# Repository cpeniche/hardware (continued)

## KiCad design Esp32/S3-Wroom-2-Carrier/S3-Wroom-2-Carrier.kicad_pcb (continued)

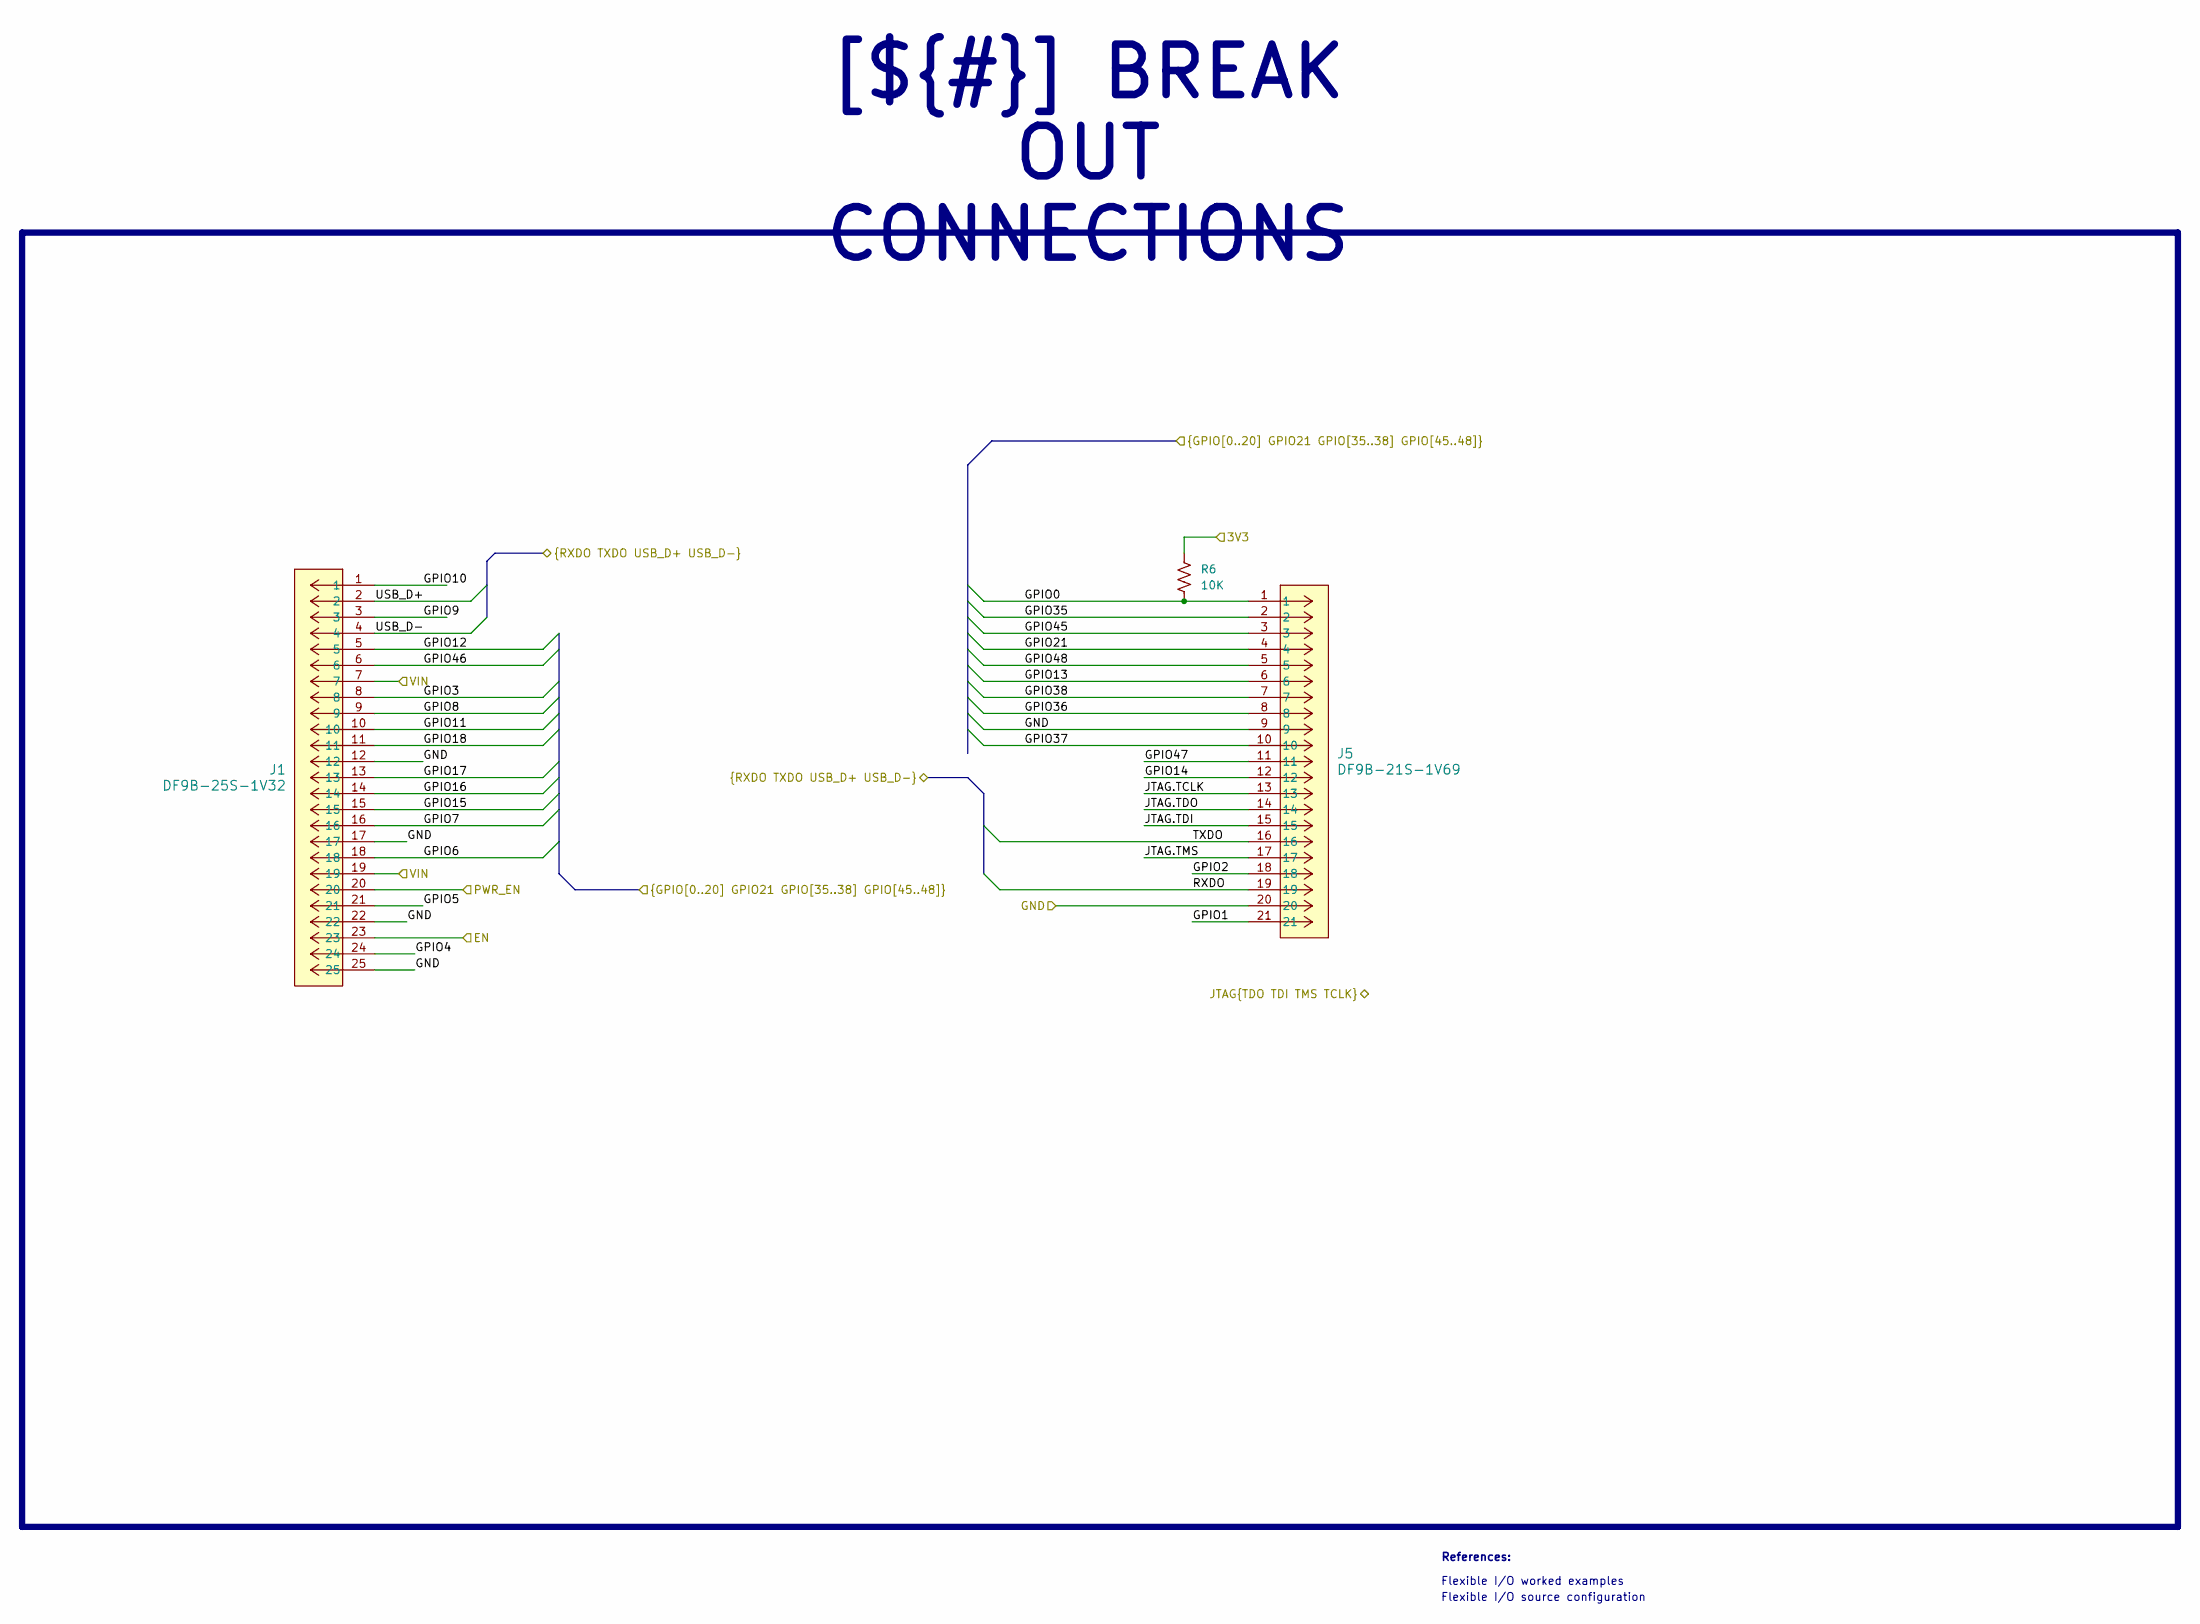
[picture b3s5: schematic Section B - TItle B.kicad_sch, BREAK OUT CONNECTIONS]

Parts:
J1: DF9B-25S-1V32; CON9_1X25_DL_DF9_HIR
J5: DF9B-21S-1V69; CONN_DF9B-21S-1V_21P_HIR
R6: 10K; R_0805_2012Metric_Pad1.20x1.40mm_HandSolder

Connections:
+3V3: R6.1; also elsewhere on the board
/Project Architecture/Break Out Connection/GPIO0: J5.1, R6.2; also elsewhere on the board
/Project Architecture/Break Out Connection/GPIO1: J5.21; also elsewhere on the board
/Project Architecture/Break Out Connection/GPIO2: J5.18; also elsewhere on the board
/Project Architecture/Break Out Connection/GPIO3: J1.8; also elsewhere on the board
/Project Architecture/Break Out Connection/GPIO4: J1.24; also elsewhere on the board
/Project Architecture/Break Out Connection/GPIO5: J1.21; also elsewhere on the board
/Project Architecture/Break Out Connection/GPIO6: J1.18; also elsewhere on the board
/Project Architecture/Break Out Connection/GPIO7: J1.16; also elsewhere on the board
/Project Architecture/Break Out Connection/GPIO8: J1.9; also elsewhere on the board
/Project Architecture/Break Out Connection/GPIO9: J1.3; also elsewhere on the board
/Project Architecture/Break Out Connection/GPIO10: J1.1; also elsewhere on the board
/Project Architecture/Break Out Connection/GPIO11: J1.10; also elsewhere on the board
/Project Architecture/Break Out Connection/GPIO12: J1.5; also elsewhere on the board
/Project Architecture/Break Out Connection/GPIO13: J5.6; also elsewhere on the board
/Project Architecture/Break Out Connection/GPIO14: J5.12; also elsewhere on the board
/Project Architecture/Break Out Connection/GPIO15: J1.15; also elsewhere on the board
/Project Architecture/Break Out Connection/GPIO16: J1.14; also elsewhere on the board
/Project Architecture/Break Out Connection/GPIO17: J1.13; also elsewhere on the board
/Project Architecture/Break Out Connection/GPIO18: J1.11; also elsewhere on the board
/Project Architecture/Break Out Connection/GPIO21: J5.4; also elsewhere on the board
/Project Architecture/Break Out Connection/GPIO35: J5.2; also elsewhere on the board
/Project Architecture/Break Out Connection/GPIO36: J5.8; also elsewhere on the board
/Project Architecture/Break Out Connection/GPIO37: J5.10; also elsewhere on the board
/Project Architecture/Break Out Connection/GPIO38: J5.7; also elsewhere on the board
/Project Architecture/Break Out Connection/GPIO45: J5.3; also elsewhere on the board
/Project Architecture/Break Out Connection/GPIO46: J1.6; also elsewhere on the board
/Project Architecture/Break Out Connection/GPIO47: J5.11; also elsewhere on the board
/Project Architecture/Break Out Connection/GPIO48: J5.5; also elsewhere on the board
/Project Architecture/Break Out Connection/JTAG.TCLK: J5.13; also elsewhere on the board
/Project Architecture/Break Out Connection/JTAG.TDI: J5.15; also elsewhere on the board
/Project Architecture/Break Out Connection/JTAG.TDO: J5.14; also elsewhere on the board
/Project Architecture/Break Out Connection/JTAG.TMS: J5.17; also elsewhere on the board
/Project Architecture/Break Out Connection/RXDO: J5.19; also elsewhere on the board
/Project Architecture/Break Out Connection/TXDO: J5.16; also elsewhere on the board
/Project Architecture/Break Out Connection/USB_D+: J1.2; also elsewhere on the board
/Project Architecture/Break Out Connection/USB_D-: J1.4; also elsewhere on the board
/Project Architecture/EN: J1.23; also elsewhere on the board
/Project Architecture/PWR_EN: J1.20; also elsewhere on the board
/Project Architecture/VIN: J1.7, J1.19; also elsewhere on the board
GND: J1.12, J1.17, J1.22, J1.25, J5.9, J5.20; also elsewhere on the board

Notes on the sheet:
Flexible I/O worked examples
References:
Flexible I/O source configuration
[${#}] ${TITLE}

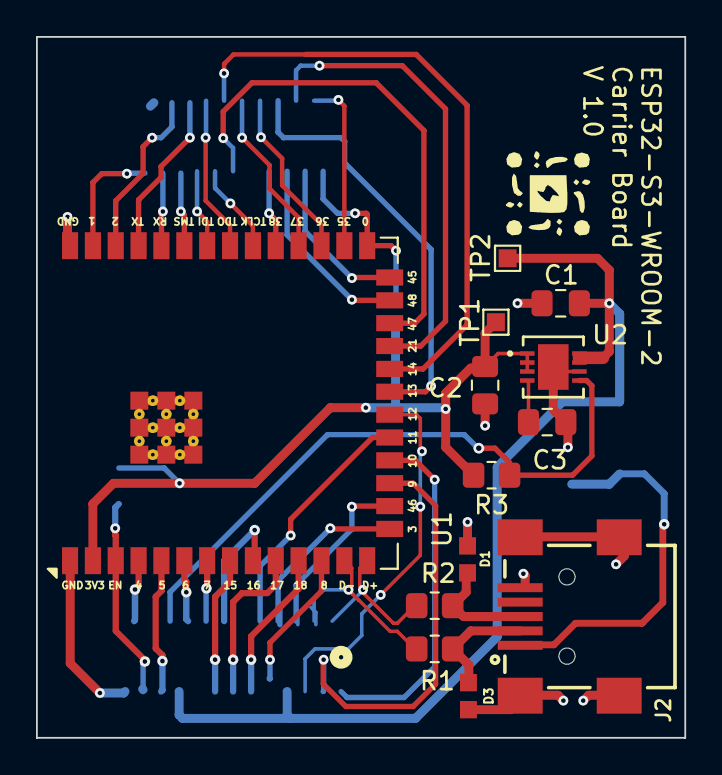
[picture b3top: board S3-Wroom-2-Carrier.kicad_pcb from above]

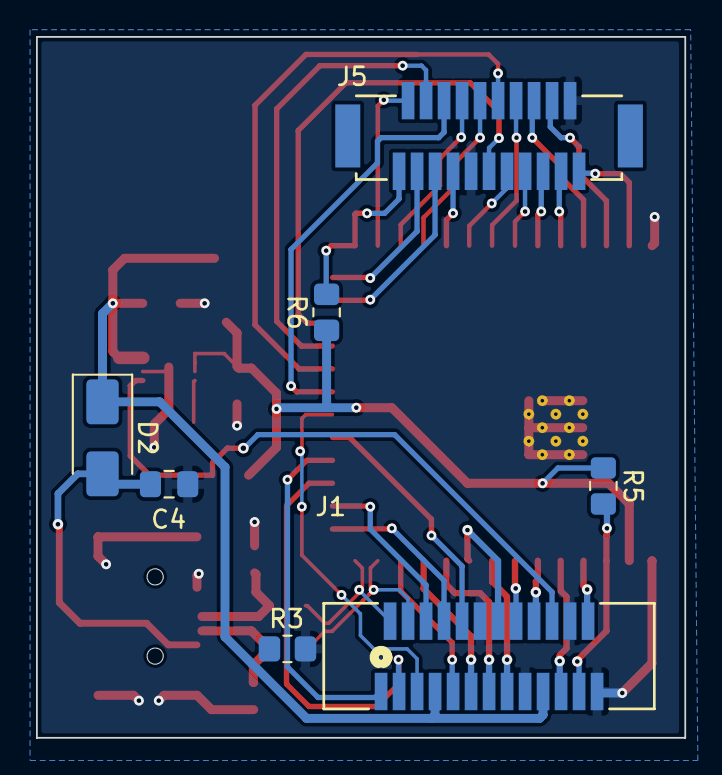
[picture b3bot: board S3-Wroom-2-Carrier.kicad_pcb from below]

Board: 2 copper layers, 36.0 x 38.9 mm, 20 parts (7 on the bottom side), 45 nets.

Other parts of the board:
R3#2: 5K1; R_0805_2012Metric_Pad1.20x1.40mm_HandSolder

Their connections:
GND: R3#2.1; also elsewhere on the board

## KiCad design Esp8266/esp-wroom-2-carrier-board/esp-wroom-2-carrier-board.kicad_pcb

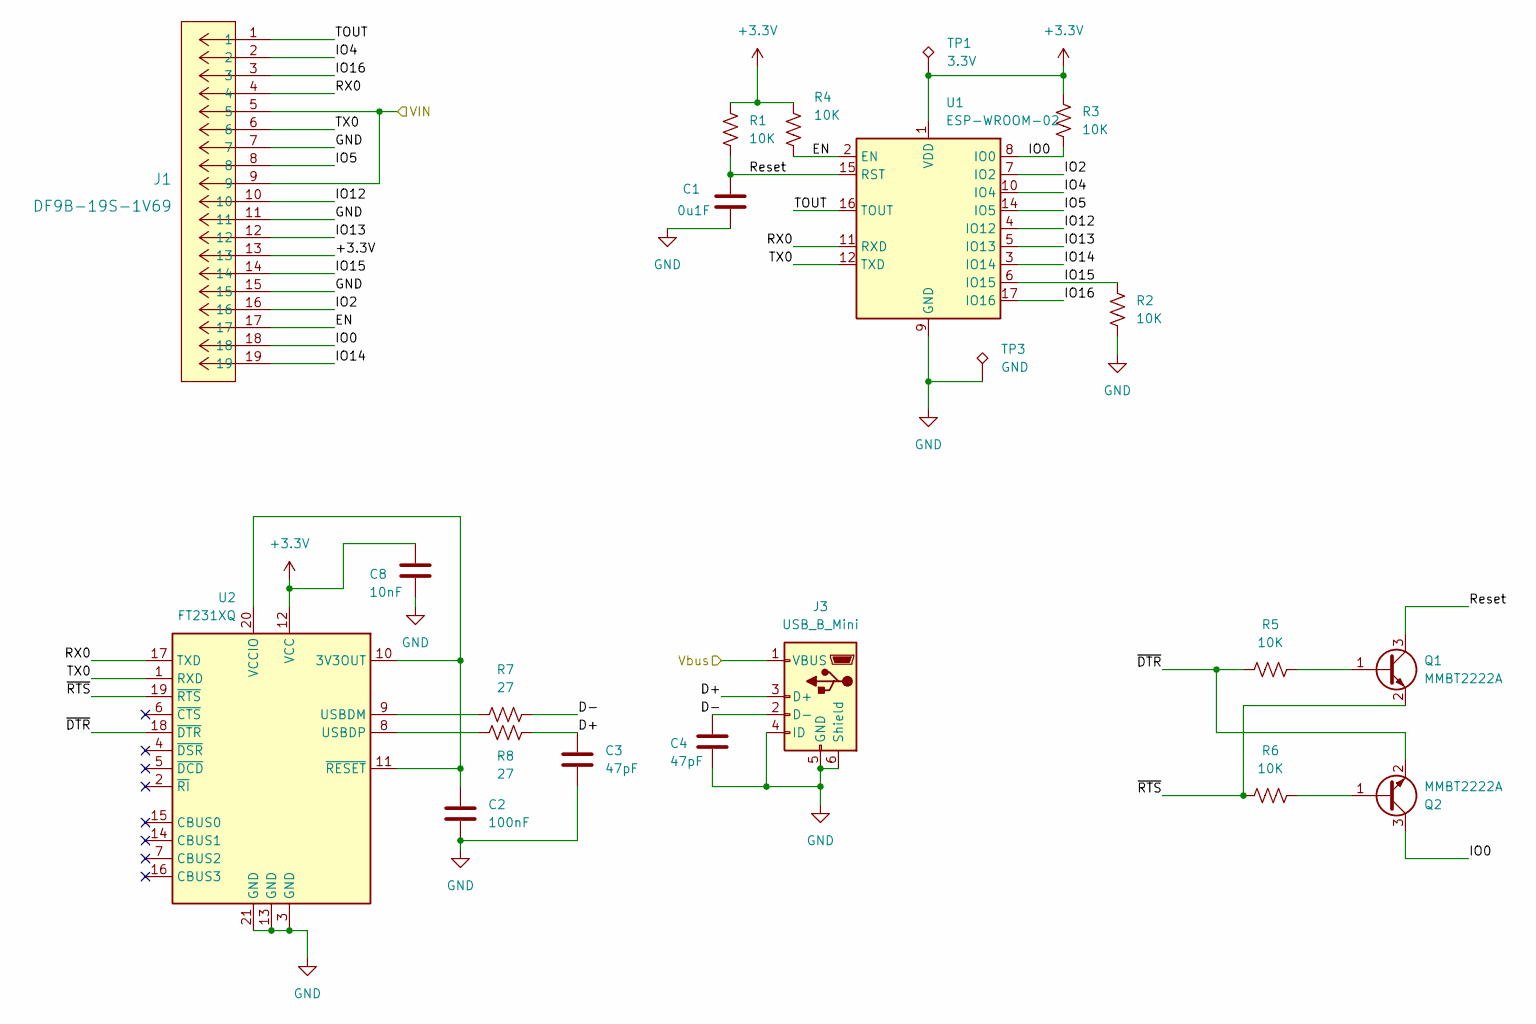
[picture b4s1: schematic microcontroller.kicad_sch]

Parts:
C1: 0u1F; C_0805_2012Metric_Pad1.18x1.45mm_HandSolder
C2: 100nF; C_0805_2012Metric_Pad1.18x1.45mm_HandSolder
C3, C4: 47pF; C_0805_2012Metric_Pad1.18x1.45mm_HandSolder
C8: 10nF; C_0805_2012Metric_Pad1.18x1.45mm_HandSolder
J1: DF9B-19S-1V69; CON9_1X19_DL_DF9_HIR
J3: USB_B_Mini; USB_Mini-B_Lumberg_2486_01_Horizontal
Q1, Q2: MMBT2222A; SOT-23
R1, R2, R3, R4, R5, R6: 10K; R_0805_2012Metric_Pad1.20x1.40mm_HandSolder
R7, R8: 27; R_0805_2012Metric_Pad1.20x1.40mm_HandSolder
TP1: 3.3V; TestPoint_THTPad_D1.0mm_Drill0.5mm
TP3: GND; TestPoint_THTPad_D1.0mm_Drill0.5mm
U1: ESP-WROOM-02
U2: FT231XQ; QFN-20-1EP_4x4mm_P0.5mm_EP2.5x2.5mm

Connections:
+3.3V: C8.1, J1.13, R1.1, R3.1, R4.1, TP1.1, U1.1 (VDD), U2.12 (VCC); also elsewhere on the board
/Microcontroller/D+: C3.1, J3.3 (D+), R8.2
/Microcontroller/D-: C4.1, J3.2 (D-), R7.2
/Microcontroller/EN: J1.17, R4.2, U1.2 (EN)
/Microcontroller/IO0: J1.18, Q2.3 (C), R3.2, U1.8 (IO0)
/Microcontroller/IO2: J1.16, U1.7 (IO2)
/Microcontroller/IO4: J1.2, U1.10 (IO4)
/Microcontroller/IO5: J1.8, U1.14 (IO5)
/Microcontroller/IO12: J1.10, U1.4 (IO12)
/Microcontroller/IO13: J1.12, U1.5 (IO13)
/Microcontroller/IO14: J1.19, U1.3 (IO14)
/Microcontroller/IO15: J1.14, R2.1, U1.6 (IO15)
/Microcontroller/IO16: J1.3, U1.17 (IO16)
/Microcontroller/RX0: J1.4, U1.11 (RXD), U2.17 (TXD)
/Microcontroller/Reset: C1.1, Q1.3 (C), R1.2, U1.15 (RST)
/Microcontroller/TOUT: J1.1, U1.16 (TOUT)
/Microcontroller/TX0: J1.6, U1.12 (TXD), U2.1 (RXD)
/Microcontroller/VIN: J1.5, J1.9; also elsewhere on the board
/Microcontroller/Vbus: J3.1 (VBUS); also elsewhere on the board
/Microcontroller/~DTR: Q2.2 (E), R5.1, U2.18 (~DTR)
/Microcontroller/~RTS: Q1.2 (E), R6.1, U2.19 (~RTS)
GND: C1.2, C2.2, C3.2, C4.2, C8.2, J1.7, J1.11, J1.15, J3.4 (ID), J3.5 (GND), J3.6 (Shield), R2.2, TP3.1, U1.9 (GND), U1.13 (GND), U1.18 (GND), U1.19 (GND), U2.3 (GND), U2.13 (GND), U2.21 (GND); also elsewhere on the board
unnamed: Q1.1 (B), R5.2
unnamed: Q2.1 (B), R6.2
unnamed: C2.1, U2.10 (3V3OUT), U2.11 (~RESET), U2.20 (VCCIO)
unnamed: R7.1, U2.9 (USBDM)
unnamed: R8.1, U2.8 (USBDP)

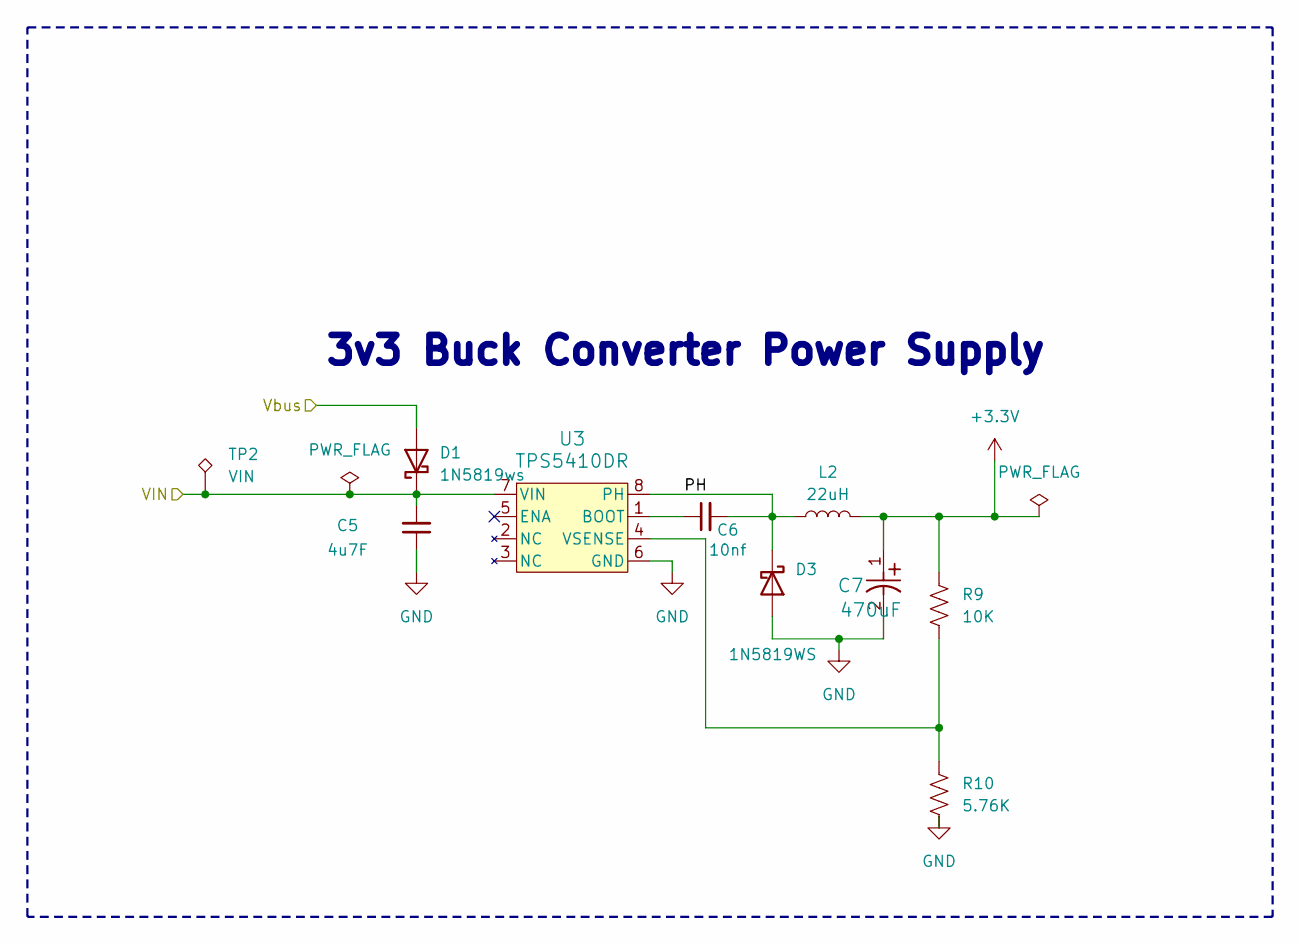
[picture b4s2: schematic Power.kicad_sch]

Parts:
C5: 4u7F; C_0805_2012Metric_Pad1.18x1.45mm_HandSolder
C6: 10nf; C_0805_2012Metric_Pad1.18x1.45mm_HandSolder
C7: 470uF; TAJD_AVX
D1: 1N5819ws; D_SOD-323
D3: 1N5819WS; D_SOD-323
L2: 22uH; MPI40-V2
R9: 10K; R_0805_2012Metric_Pad1.20x1.40mm_HandSolder
R10: 5.76K; R_0805_2012Metric_Pad1.20x1.40mm_HandSolder
TP2: VIN; TestPoint_THTPad_D1.0mm_Drill0.5mm
U3: TPS5410DR; SOIC-8-1EP_3.9x4.9mm_P1.27mm

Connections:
+3.3V: C7.1, L2.2, R9.1; also elsewhere on the board
/Microcontroller/VIN: C5.2, D1.1 (K), TP2.1, U3.7 (VIN); also elsewhere on the board
/Microcontroller/Vbus: D1.2 (A); also elsewhere on the board
/Power/PH: C6.2, D3.1 (K), L2.1, U3.8 (PH)
GND: C5.1, C7.2, D3.2 (A), R10.2, U3.6 (GND); also elsewhere on the board
unnamed: C6.1, U3.1 (BOOT)
unnamed: R9.2, R10.1, U3.4 (VSENSE)

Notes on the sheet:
3v3 Buck Converter Power Supply

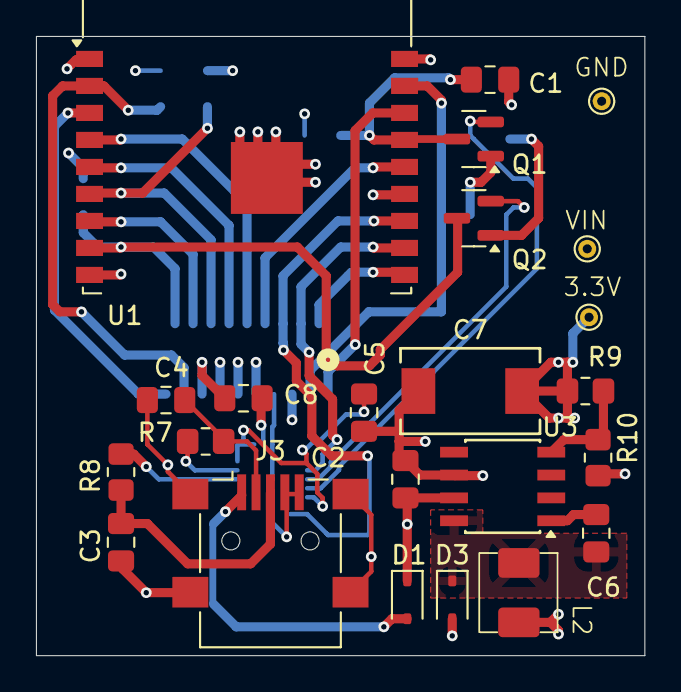
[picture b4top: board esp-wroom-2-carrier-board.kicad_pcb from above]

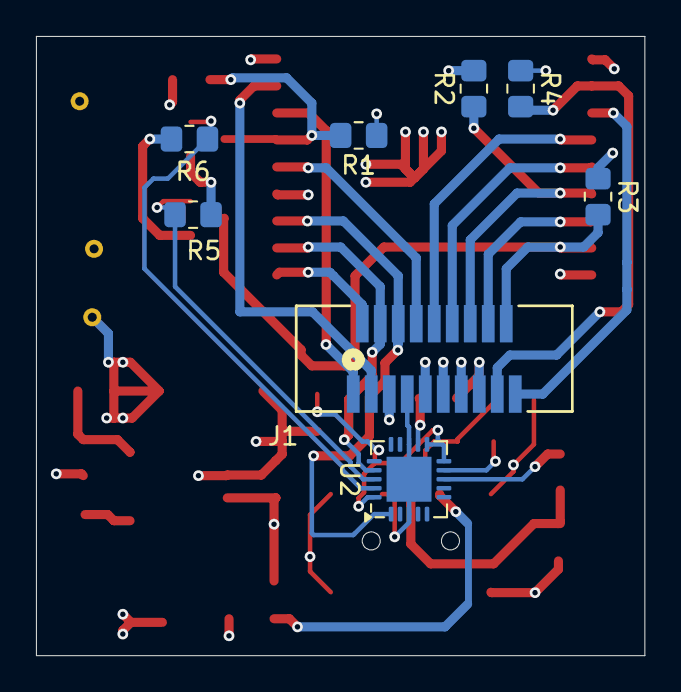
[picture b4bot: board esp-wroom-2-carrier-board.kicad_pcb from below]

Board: 4 copper layers, 33.8 x 34.4 mm, 31 parts (8 on the bottom side), 30 nets.

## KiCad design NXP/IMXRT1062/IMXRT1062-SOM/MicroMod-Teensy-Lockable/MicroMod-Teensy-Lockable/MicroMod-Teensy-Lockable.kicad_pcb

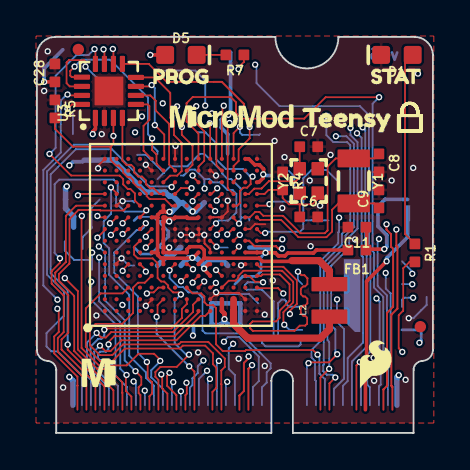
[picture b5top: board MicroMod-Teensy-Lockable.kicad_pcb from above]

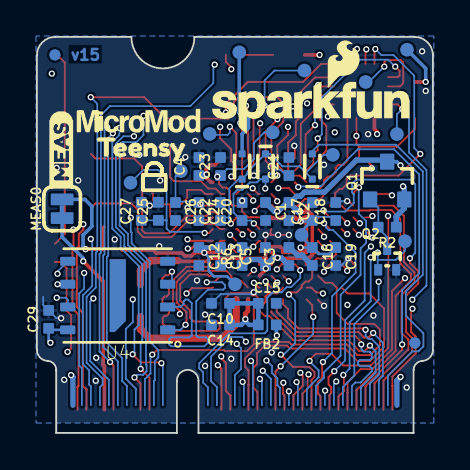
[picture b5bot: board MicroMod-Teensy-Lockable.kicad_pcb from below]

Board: 4 copper layers, 22.0 x 22.0 mm, 83 parts (53 on the bottom side), 42 nets.

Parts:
C1, C11: 2.2uF; 0402-TIGHT
C2, C14, C18, C26, C27: 4.7uF; 0402-TIGHT
C3, C4, C12, C13, C15, C17, C20, C22, C23, C24, C25, C28, C29: 0.22uF; 0402-TIGHT
C5, C16: 10nF; 0402-TIGHT
C6, C7: 12pF; 0402-TIGHT
C8, C9: 20pF; 0402-TIGHT
C10, C19, C21: 10uF; 0402-TIGHT
D1: BLUE; LED-0603
D2, D3, D4: 120mA/40V/370mV; SOD-523
D5: Yellow; LED-0603
FB1, FB2: 120Ω; 0402-TIGHT
FD1, FD2, FD3, FD4: FIDUCIALUFIDUCIAL; FIDUCIAL-MICRO
FRAME1: FRAME-LEDGER; CREATIVE_COMMONS
L2: 4.7μH; 1008(2520)
LOGO1: SFE_LOGO_NAME_FLAME.1_INCH; SFE_LOGO_NAME_FLAME_.1
LOGO2: OSHW-LOGONO_SILK; DUMMY
LOGO3: SPECIAL_INSTRUCTIONS-ORDERING; ORDERING_INSTRUCTIONS
MEAS0: SMT-JUMPER_2_NC_TRACE_SILK
Q1: 20V/4.2A/52mΩ/1.4W; SOT23-3
Q2: 20V/0.2A/8MHz/1.2Ω/1Vth; SOT-416FL
R1, R7: 1k; 0402-TIGHT
R2, R5, R6: 100k; 0402-TIGHT
R4: 2.2M; 0402-TIGHT
TP1, TP2, TP3, TP4, TP5, TP6, TP7, TP8, TP9, TP10, TP11, TP12, TP13: PAD.03X.03
U1: IMXRT1062DV10X10; IMXRT1062
U3: MKL02Z32VFG4; QFN-16
U4: W25QXX128MBIT-6X5; WSON-8-6X5-SKINNY_CENTERPAD
U$1, U$3: TEENSY2
U$4: MICROMOD_MI_LOGO_.35
U$6: SFE_LOGO_FLAME_.1
U$7, U$11: MICROMOD_LOGO_.3
U$8: MEAS2
U$9: PROG0
U$10: STAT1
U$16, U$17: LOCKED4#PNG
Y1: 32.768kHz; CRYSTAL-SMD-3.2X1.5MM
Y2: 24MHz; CRYSTAL-SMD-2.0X1.6MM

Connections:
3.3V: D2.A, Q1.2, R2.1, TP13.P$1
3.3V_CONTROLLED: C1.1, C2.1, C3.1, C4.1, C5.1, C28.1, C29.1, D5.A, FB2.1, Q1.3, R6.1, TP12.P$1, U1.E6, U1.E9, U1.F5, U1.F10, U1.J6, U1.J10, U1.K4, U1.K5, U1.N14, U1.P12, U3.1, U4.8
24MHZ_1: C7.1, U1.N11, Y2.3
24MHZ_2: C6.1, R4.2, U1.P11, Y2.1
32KHZ_1: C8.1, U1.N9, Y1.P$1
32KHZ_2: C9.1, U1.P9, Y1.P$2
32KHZ_TEST: TP1.P$1, U1.M14
BOOTMODE0: U1.F11, U3.4
DCDC_IN: C10.1, C14.1, C15.1, FB2.2, U1.L1, U1.L2
DCDC_LP: L2.1, U1.M1, U1.M2
DEBUG_EN: U1.F3, U3.15
DEBUG_SWO: U1.D10, U3.12
GND: C1.2, C2.2, C3.2, C4.2, C5.2, C6.2, C7.2, C8.2, C9.2, C10.2, C11.2, C12.2, C13.2, C14.2, C15.2, C16.2, C17.2, C18.2, C19.2, C20.2, C21.2, C22.2, C23.2, C24.2, C25.2, C26.2, C27.2, C28.2, C29.2, D1.C, Q2.2, R4.1, R5.1, U1.A1, U1.A14, U1.B5, U1.B10, U1.E2, U1.E13, U1.G7, U1.G8, U1.G14, U1.H7, U1.H8, U1.J7, U1.J8, U1.K2, U1.K6, U1.K9, U1.K13, U1.L9, U1.N1, U1.N2, U1.N5, U1.N8, U1.P1, U1.P14, U3.2, U3.17, U4.4
JTAG_MOD: U1.F13, U3.13
JTAG_TCK: U1.F12, U3.8
JTAG_TDI: U1.F14, U3.7
JTAG_TDO: U1.G13, U3.6
JTAG_TMS: U1.E14, U3.5
JTAG_TRST: R5.2, U1.G10, U1.K3, U3.3
unnamed: D1.A, R1.1
unnamed: Q1.1, Q2.3, R2.2
unnamed: C11.1, FB1.1, MEAS0.2
unnamed: R7.1, U3.11
unnamed: D5.C, R7.2
NVCC_PLL: C24.1, C26.1, TP6.P$1, U1.P10
PMIC: Q2.1, R6.2, TP2.P$1, U1.K7
PORB_RESET: U1.M7, U3.9
QSPI0: U1.P3, U4.5
QSPI1: U1.N4, U4.2
QSPI2: U1.P4, U4.3
QSPI3: U1.P5, U4.7
QSPI-CLK: U1.L4, U4.6
QSPI-CS: U1.L3, U4.1
SCK/13: R1.2, U1.D8
SWD_CLK: TP9.P$1, U3.14
SWD_DIO: TP8.P$1, U3.16
VCC: C12.1, C13.1, FB1.2, TP3.P$1, U1.N6, U1.P6
VDD_HIGH_CAP: C25.1, C27.1, TP7.P$1, U1.P8
VDD_SNVS_CAP: C23.1, TP5.P$1, U1.M10
VDD_SNVS_IN: C22.1, D2.C, D3.C, D4.C, TP4.P$1, U1.M9
VDD_SOC_IN: C16.1, C17.1, C18.1, C19.1, L2.2, TP10.P$1, U1.F6, U1.F7, U1.F8, U1.F9, U1.G6, U1.G9, U1.H6, U1.H9, U1.J5, U1.J9
VDD_USB_CAP: C20.1, C21.1, D4.A, TP11.P$1, U1.K8
